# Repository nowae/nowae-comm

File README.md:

# nowae-comm
Repository to store all communication boards project

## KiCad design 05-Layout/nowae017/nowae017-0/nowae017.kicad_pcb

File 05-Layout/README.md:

# nowae-comm

In this folder you can find the boards design files of project.
* NOWAE017 - Small adapter module for U-Blox SARA-U/SARA-G Series

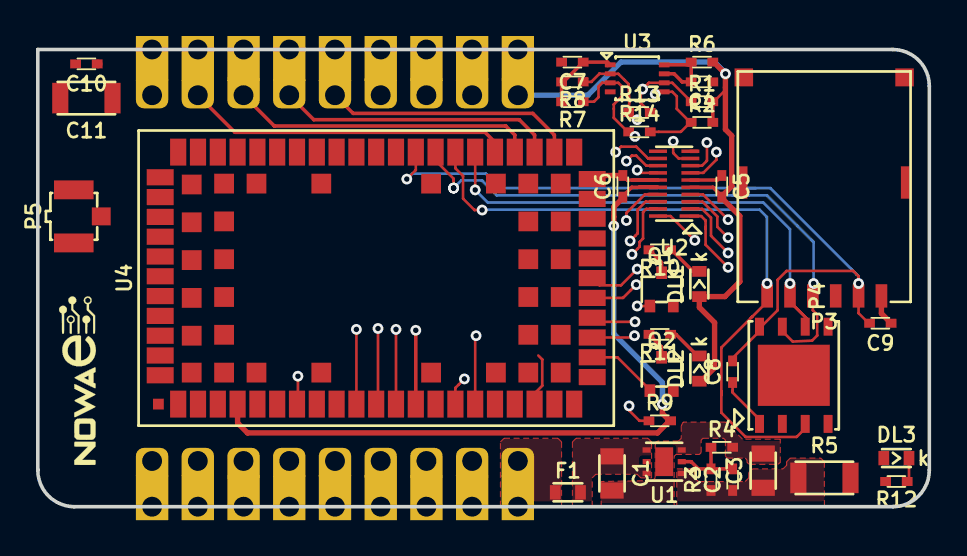
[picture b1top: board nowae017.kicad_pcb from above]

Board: 4 copper layers, 49.5 x 25.4 mm, 40 parts (1 on the bottom side), 45 nets.

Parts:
C1: 1u; CAPACITOR-0805
C2: 22p; CAPACITOR-0402
C3: 4u7; CAPACITOR-0805
C4, C5, C6, C7, C8, C9, C10: 100n; CAPACITOR-0402
C11: 10u; RESISTOR-1206
DL1, DL2, DL3: RED; LED-0603
F1: 0467.500NR; RESISTOR-0603
P1, P2: CONN_9X1; CONN-HALFHOLE-9x1-2.54
P3: NANOSIM; NANOSIM-WURTH-693043020611
P4: ESIM; ESIM-GENERIC
P5: U.FL; UFL-HIROSE-U_FL-R-SMT-1
Q1, Q2: PTDC114EU; SOT323-3
R1, R2, R7, R8: 4k7; RESISTOR-0402
R3: 249k; RESISTOR-0402
R4: 110k; RESISTOR-0402
R5: 100m; RESISTOR-1206
R6, R9: 100k; RESISTOR-0402
R10, R11, R12: 2k2; RESISTOR-0402
R13, R14: 0; RESISTOR-0402
U1: TPS73501DRV; WSON6_2.0x2.0_0.65_6+1
U2: TXB0108DQSR; USON20_4.0x2.0_0.4_20
U3: PCA9306DC; VSSOP8_2.4x2.1_0.5
U4: SARA-U201; HSPA-SARAU2

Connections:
+1.8V: C6.1, C7.1, R7.2, R8.2, R9.2, U2.16, U3.1, U4.4
+3.8V: C10.1, C11.1, R5.2, U4.51, U4.52, U4.53
+VDIO: C5.2, DL1.1, DL2.1, P2.1, R1.2, R2.2, R6.2, U2.5
+VIN: F1.1, P1.1
/CODEC_CLK: P2.9, U4.19
/I2C_SCL: R8.1, R13.1, U3.2, U4.27
/I2C_SCL_EXT: P1.9, R1.1, R13.2, U3.6
/I2C_SDA: R7.1, R14.1, U3.3, U4.26
/I2C_SDA_EXT: P1.8, R2.1, R14.2, U3.5
/PCM_CLK: P2.7, U4.36
/PCM_DIN: P2.8, U4.37
/PCM_DOUT: P2.6, U4.35
/PCM_SYNC: P2.5, U4.34
/SARA_ANTENNA: P5.1, U4.56
/SARA_GPIO3: U2.14, U4.24
/SARA_GPIO3_EXT: P2.3, U2.7
/SARA_GPIO4: U2.13, U4.25
/SARA_GPIO4_EXT: P2.4, U2.8
/SARA_PWRON: R9.1, U4.15
/SARA_STS_LED: Q2.1, U4.23
/SARA_TX_LED: Q1.1, U4.16
/SIM_CLK: P3.C3, P4.6, U4.38
/SIM_IO: P3.C7, P4.3, U4.39
/SIM_RST: P3.C2, P4.7, U4.40
/SIM_VCC: C8.2, C9.2, P3.C1, P4.8, U4.41
/UART_CTS: U2.18, U4.11
/UART_CTS_EXT: P1.5, U2.3
/UART_RI: U2.12, U4.7
/UART_RI_EXT: P1.7, U2.9
/UART_RTS: U2.17, U4.10
/UART_RTS_EXT: P1.6, U2.4
/UART_RXD: U2.20, U4.13
/UART_RXD_EXT: P1.3, U2.1
/UART_TXD: U2.19, U4.12
/UART_TXD_EXT: P1.4, U2.2
GND: C1.2, C3.2, C4.1, C5.1, C6.2, C7.2, C8.1, C9.1, C10.2, C11.2, P1.2, P3.C5, P4.1, P5.2, Q1.2, Q2.2, R4.2, R12.2, U1.3, U2.6, U2.15, U3.4, U4.1, U4.3, U4.5, U4.14, U4.20, U4.21, U4.22, U4.30, U4.32, U4.33, U4.43, U4.50, U4.54, U4.55, U4.57, U4.58, U4.59, U4.60, U4.61, U4.63, U4.64, U4.65, U4.66, U4.67, U4.68, U4.69, U4.70, U4.71, U4.72, U4.73, U4.74, U4.75, U4.76, U4.77, U4.78, U4.79, U4.80, U4.81, U4.82, U4.83, U4.84, U4.85, U4.86, U4.87, U4.88, U4.89, U4.90, U4.91, U4.92, U4.93, U4.94, U4.95, U4.96
unnamed: C1.1, F1.2, U1.4, U1.6
unnamed: C2.1, C3.1, DL3.1, R3.1, R5.1, U1.1
unnamed: C2.2, R3.2, R4.1, U1.2
unnamed: C4.2, R6.1, U3.7, U3.8
unnamed: DL1.2, R10.1
unnamed: DL2.2, R11.1
unnamed: DL3.2, R12.1
unnamed: Q1.3, R10.2
unnamed: Q2.3, R11.2

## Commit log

2018-09-06 Added repository structure
2018-09-07 Added basic project structure for NOWAE017-0
2018-10-01 Added SARA-U2 module
2018-10-09 Added sim connector
2018-10-09 WiP: schematich
2018-10-12 WiP on schematic: added other pins from SARA module and added transistor for leds
2018-10-12 Added embedded sim
2018-10-12 Added footprint library list file
2018-10-12 WiP on schematic
2018-10-13 Added u.fl connector for antenna connection
2018-10-15 Added voltage traslater for I2C signals and connector for external pads
2018-10-19 Added voltage translator for each external signals. Added sponsor logo.
2018-10-22 Added voltage regulator for 3.8V. Added RI pins to external output.
2018-10-22 Added shunt before SARA Module.
2018-10-24 Added footprint for external connector and started pcb (nowae017-0)
2018-10-25 Moved shunt after bypass capacitor. Added power-on led
2018-10-25 WiP placement (nowae017-0)
2018-10-26 Placement complete (nowae017-0)
2018-10-29 WiP: routing (nowae017-0)
2018-10-30 Added resistors to bypass I2C voltage translator
2018-10-30 WiP routing (nowae017-0)
2018-10-31 WiP routing of supply zone (nowae017-0)
